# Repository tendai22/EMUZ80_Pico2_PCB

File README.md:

# EMUZ80_Pico2_PCB
KiCad PCB for emuz80_pico2

## WeAct RP2350B Core Board での動作

GPIO23を D7 に割り当てているが、D7 だけ L に落ちてくれない。

一瞬 L になるが、次の瞬間に H に戻っている。

blink で GPIO23 を指定したときは動作している。

Pimoroni 2350 の試作基板では動作している。

ハードウェアの違いによると考えられる。

基板の配線違いか、5.1kΩのプルアップが悪さをしていると考えた。

導通を見る限り怪しいところとつながっている様子はない。

結局 5.1kΩプルアップ抵抗をちぎり取って動作するようになった。なんとも。

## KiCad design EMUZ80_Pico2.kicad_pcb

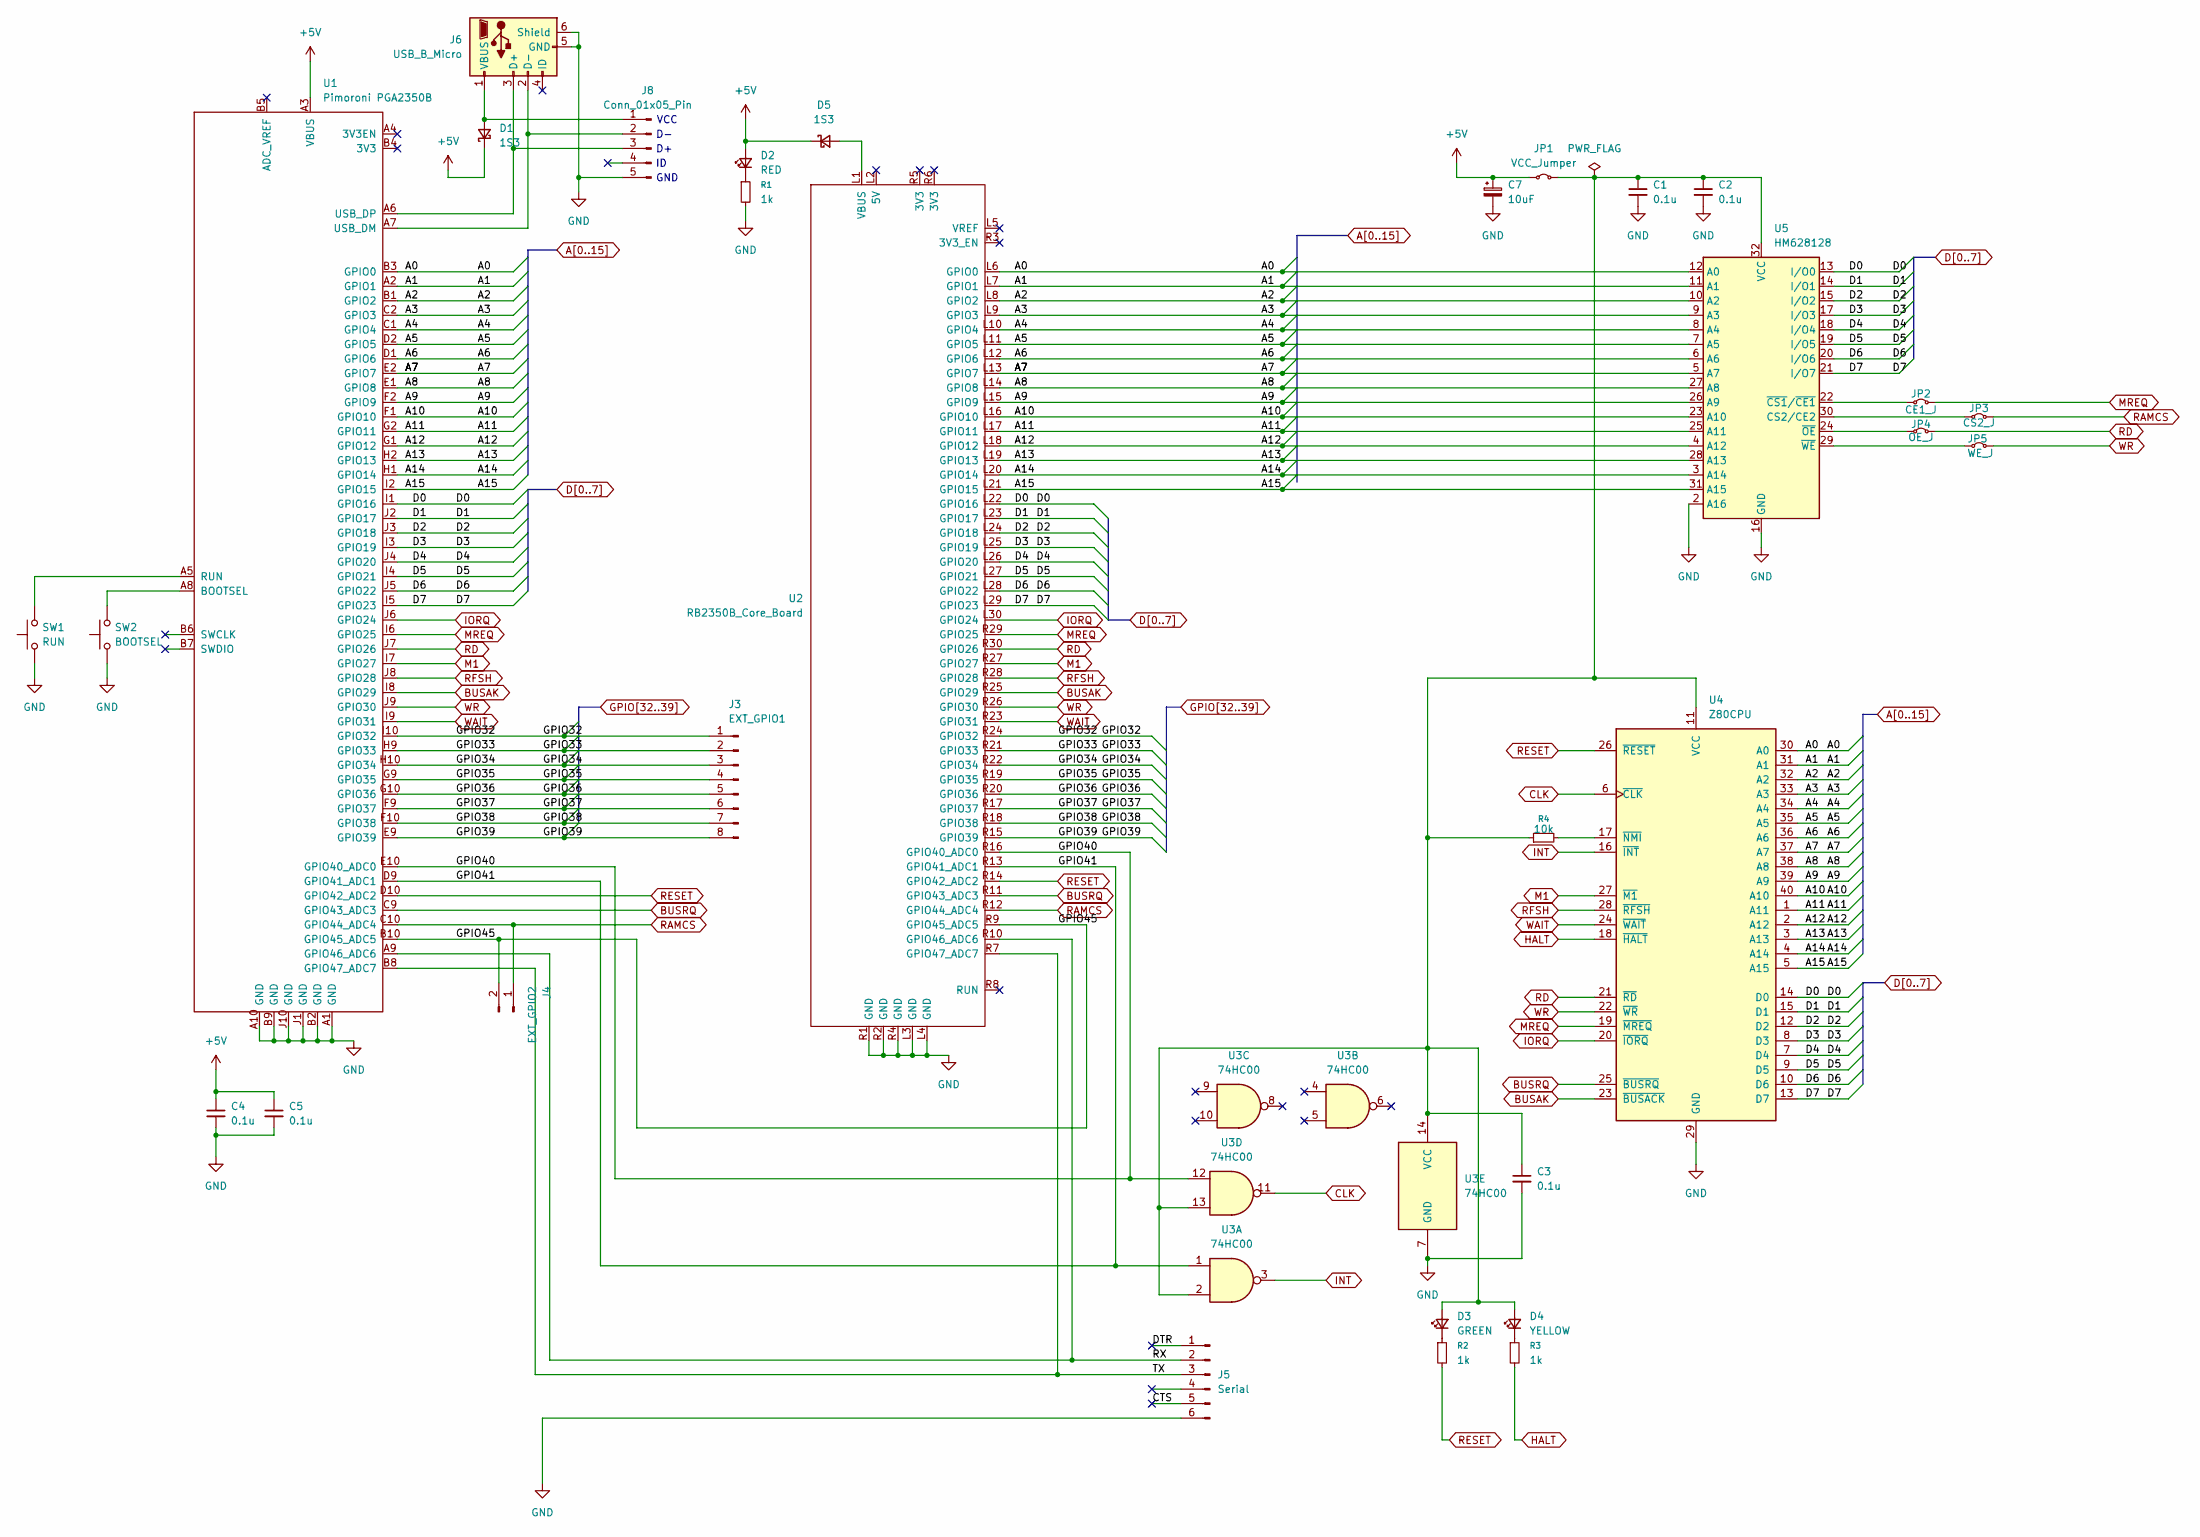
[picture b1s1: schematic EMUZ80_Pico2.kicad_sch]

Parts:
C1, C2, C3, C4, C5: 0.1u; C_Disc_D3.0mm_W1.6mm_P2.50mm
C7: 10uF; CP_Radial_D5.0mm_P2.50mm
D1, D5: 1S3; D_DO-34_SOD68_P7.62mm_Horizontal
D2: RED; LED_D3.0mm
D3: GREEN; LED_D3.0mm
D4: YELLOW; LED_D3.0mm
J3: EXT_GPIO1; PinHeader_1x08_P2.54mm_Vertical
J4: EXT_GPIO2; PinHeader_1x02_P2.54mm_Vertical
J5: Serial; PinHeader_1x06_P2.54mm_Horizontal_NoFeet
J6: USB_B_Micro; USB_Micro-B_Hirose_ZX62-B-5PA
J8: Conn_01x05_Pin; PinHeader_1x05_P2.54mm_Vertical
JP1: VCC_Jumper; SolderJumper-2_P1.3mm_Bridged_RoundedPad1.0x1.5mm
JP2: CE1_J; SolderJumper-2_P1.3mm_Bridged_RoundedPad1.0x1.5mm
JP3: CS2_J; SolderJumper-2_P1.3mm_Bridged_RoundedPad1.0x1.5mm
JP4: OE_J; SolderJumper-2_P1.3mm_Bridged_RoundedPad1.0x1.5mm
JP5: WE_J; SolderJumper-2_P1.3mm_Bridged_RoundedPad1.0x1.5mm
R1, R2, R3: 1k; R_Axial_L5.5mm_D2.0mm_P7.62mm_Horizontal
R4: 10k; R_Axial_L5.5mm_D2.0mm_P7.62mm_Horizontal
SW1: RUN; Tact_SW
SW2: BOOTSEL; Tact_SW
U1: Pimoroni PGA2350B; PLCC-64_THT-Socket
U2: RB2350B_Core_Board
U3: 74HC00; DIP-14_W7.62mm_Socket
U4: Z80CPU; DIP-40_SidePin_Z80
U5: HM628128; DIP-32_W15.24mm_OvalPads

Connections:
+5V: C4.1, C5.1, C7.1, D1.1 (K), D2.2 (A), D5.1 (K), JP1.1 (A), U1.A3 (VBUS)
/CTS: J5.5
/DTR: J5.1
/GPIO40: U1.E10 (GPIO40_ADC0), U2.R16 (GPIO40_ADC0), U3.12
/GPIO41: U1.D9 (GPIO41_ADC1), U2.R13 (GPIO41_ADC1), U3.1
/GPIO45: J4.2, U1.B10 (GPIO45_ADC5), U2.R9 (GPIO45_ADC5)
/RX: J5.2, U1.A9 (GPIO46_ADC6), U2.R10 (GPIO46_ADC6)
/TX: J5.3, U1.B8 (GPIO47_ADC7), U2.R7 (GPIO47_ADC7)
A0: U1.B3 (GPIO0), U2.L6 (GPIO0), U4.30 (A0), U5.12 (A0)
A1: U1.A2 (GPIO1), U2.L7 (GPIO1), U4.31 (A1), U5.11 (A1)
A2: U1.B1 (GPIO2), U2.L8 (GPIO2), U4.32 (A2), U5.10 (A2)
A3: U1.C2 (GPIO3), U2.L9 (GPIO3), U4.33 (A3), U5.9 (A3)
A4: U1.C1 (GPIO4), U2.L10 (GPIO4), U4.34 (A4), U5.8 (A4)
A5: U1.D2 (GPIO5), U2.L11 (GPIO5), U4.35 (A5), U5.7 (A5)
A6: U1.D1 (GPIO6), U2.L12 (GPIO6), U4.36 (A6), U5.6 (A6)
A7: U1.E2 (GPIO7), U2.L13 (GPIO7), U4.37 (A7), U5.5 (A7)
A8: U1.E1 (GPIO8), U2.L14 (GPIO8), U4.38 (A8), U5.27 (A8)
A9: U1.F2 (GPIO9), U2.L15 (GPIO9), U4.39 (A9), U5.26 (A9)
A10: U1.F1 (GPIO10), U2.L16 (GPIO10), U4.40 (A10), U5.23 (A10)
A11: U1.G2 (GPIO11), U2.L17 (GPIO11), U4.1 (A11), U5.25 (A11)
A12: U1.G1 (GPIO12), U2.L18 (GPIO12), U4.2 (A12), U5.4 (A12)
A13: U1.H2 (GPIO13), U2.L19 (GPIO13), U4.3 (A13), U5.28 (A13)
A14: U1.H1 (GPIO14), U2.L20 (GPIO14), U4.4 (A14), U5.3 (A14)
A15: U1.I2 (GPIO15), U2.L21 (GPIO15), U4.5 (A15), U5.31 (A15)
BUSAK: U1.I8 (GPIO29), U2.R25 (GPIO29), U4.23 (~BUSACK)
BUSRQ: U1.C9 (GPIO43_ADC3), U2.R11 (GPIO43_ADC3), U4.25 (~BUSRQ)
CLK: U3.11, U4.6 (~CLK)
D0: U1.I1 (GPIO16), U2.L22 (GPIO16), U4.14 (D0), U5.13 (I/O0)
D1: U1.J2 (GPIO17), U2.L23 (GPIO17), U4.15 (D1), U5.14 (I/O1)
D2: U1.J3 (GPIO18), U2.L24 (GPIO18), U4.12 (D2), U5.15 (I/O2)
D3: U1.I3 (GPIO19), U2.L25 (GPIO19), U4.8 (D3), U5.17 (I/O3)
D4: U1.J4 (GPIO20), U2.L26 (GPIO20), U4.7 (D4), U5.18 (I/O4)
D5: U1.I4 (GPIO21), U2.L27 (GPIO21), U4.9 (D5), U5.19 (I/O5)
D6: U1.J5 (GPIO22), U2.L28 (GPIO22), U4.10 (D6), U5.20 (I/O6)
D7: U1.I5 (GPIO23), U2.L29 (GPIO23), U4.13 (D7), U5.21 (I/O7)
GND: C1.2, C2.2, C3.2, C4.2, C5.2, C7.2, J5.6, J6.5 (GND), J6.6 (Shield), J8.5, R1.2, SW1.1, SW2.1, U1.A1 (GND), U1.A10 (GND), U1.B2 (GND), U1.B9 (GND), U1.J1 (GND), U1.J10 (GND), U2.L3 (GND), U2.L4 (GND), U2.R1 (GND), U2.R2 (GND), U2.R4 (GND), U3.7 (GND), U4.29 (GND), U5.2 (A16), U5.16 (GND)
GPIO32: J3.1, U1.I10 (GPIO32), U2.R24 (GPIO32)
GPIO33: J3.2, U1.H9 (GPIO33), U2.R21 (GPIO33)
GPIO34: J3.3, U1.H10 (GPIO34), U2.R22 (GPIO34)
GPIO35: J3.4, U1.G9 (GPIO35), U2.R19 (GPIO35)
GPIO36: J3.5, U1.G10 (GPIO36), U2.R20 (GPIO36)
GPIO37: J3.6, U1.F9 (GPIO37), U2.R17 (GPIO37)
GPIO38: J3.7, U1.F10 (GPIO38), U2.R18 (GPIO38)
GPIO39: J3.8, U1.E9 (GPIO39), U2.R15 (GPIO39)
HALT: R3.2, U4.18 (~HALT)
INT: U3.3, U4.16 (~INT)
IORQ: U1.J6 (GPIO24), U2.L30 (GPIO24), U4.20 (~IORQ)
M1: U1.I7 (GPIO27), U2.R27 (GPIO27), U4.27 (~M1)
MREQ: JP2.2 (B), U1.I6 (GPIO25), U2.R29 (GPIO25), U4.19 (~MREQ)
unnamed: D1.2 (A), J6.1 (VBUS), J8.1
unnamed: D2.1 (K), R1.1
unnamed: C1.1, C2.1, C3.1, D3.2 (A), D4.2 (A), JP1.2 (B), R4.1, U3.2, U3.13, U3.14 (VCC), U4.11 (VCC), U5.32 (VCC)
unnamed: D3.1 (K), R2.1
unnamed: D4.1 (K), R3.1
unnamed: D5.2 (A), U2.L1 (VBUS)
unnamed: J6.3 (D+), J8.3, U1.A6 (USB_DP)
unnamed: J6.2 (D-), J8.2, U1.A7 (USB_DM)
unnamed: JP2.1 (A), U5.22 (~CS1/~CE1)
unnamed: JP3.1 (A), U5.30 (CS2/CE2)
unnamed: JP4.1 (A), U5.24 (~OE)
unnamed: JP5.1 (A), U5.29 (~WE)
unnamed: SW2.2, U1.A8 (BOOTSEL)
unnamed: SW1.2, U1.A5 (RUN)
unnamed: R4.2, U4.17 (~NMI)
RAMCS: J4.1, JP3.2 (B), U1.C10 (GPIO44_ADC4), U2.R12 (GPIO44_ADC4)
RD: JP4.2 (B), U1.J7 (GPIO26), U2.R30 (GPIO26), U4.21 (~RD)
RESET: R2.2, U1.D10 (GPIO42_ADC2), U2.R14 (GPIO42_ADC2), U4.26 (~RESET)
RFSH: U1.J8 (GPIO28), U2.R28 (GPIO28), U4.28 (~RFSH)
WAIT: U1.I9 (GPIO31), U2.R23 (GPIO31), U4.24 (~WAIT)
WR: JP5.2 (B), U1.J9 (GPIO30), U2.R26 (GPIO30), U4.22 (~WR)

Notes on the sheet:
GND
VCC

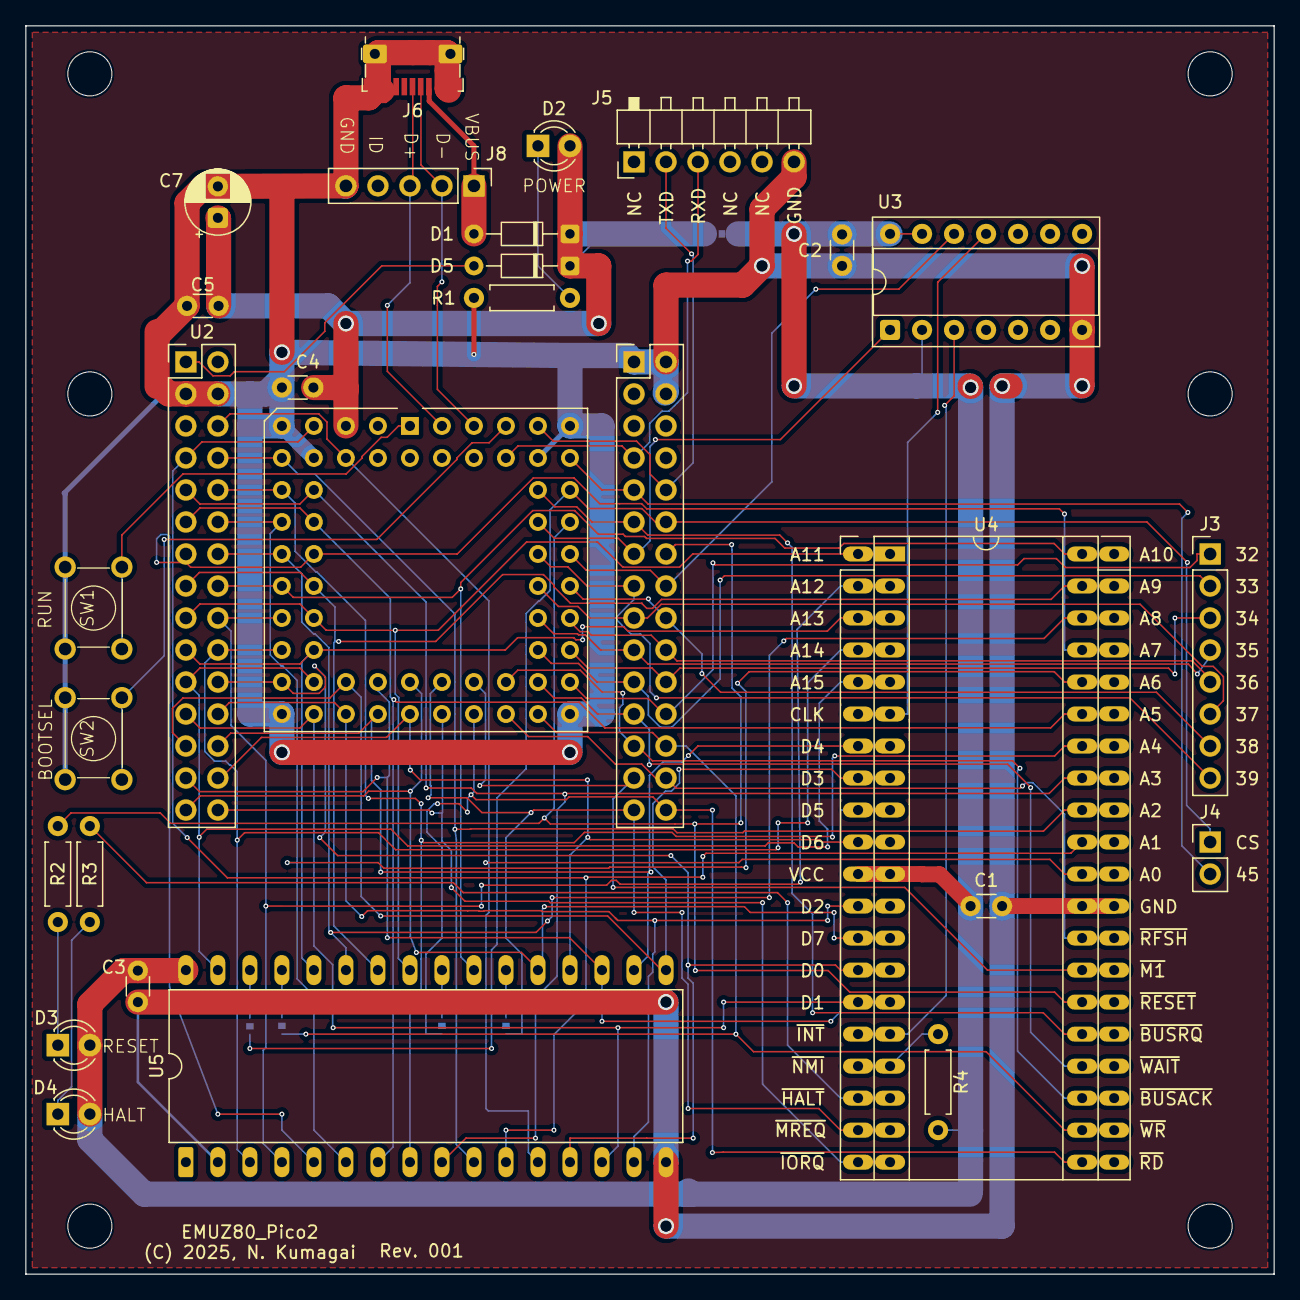
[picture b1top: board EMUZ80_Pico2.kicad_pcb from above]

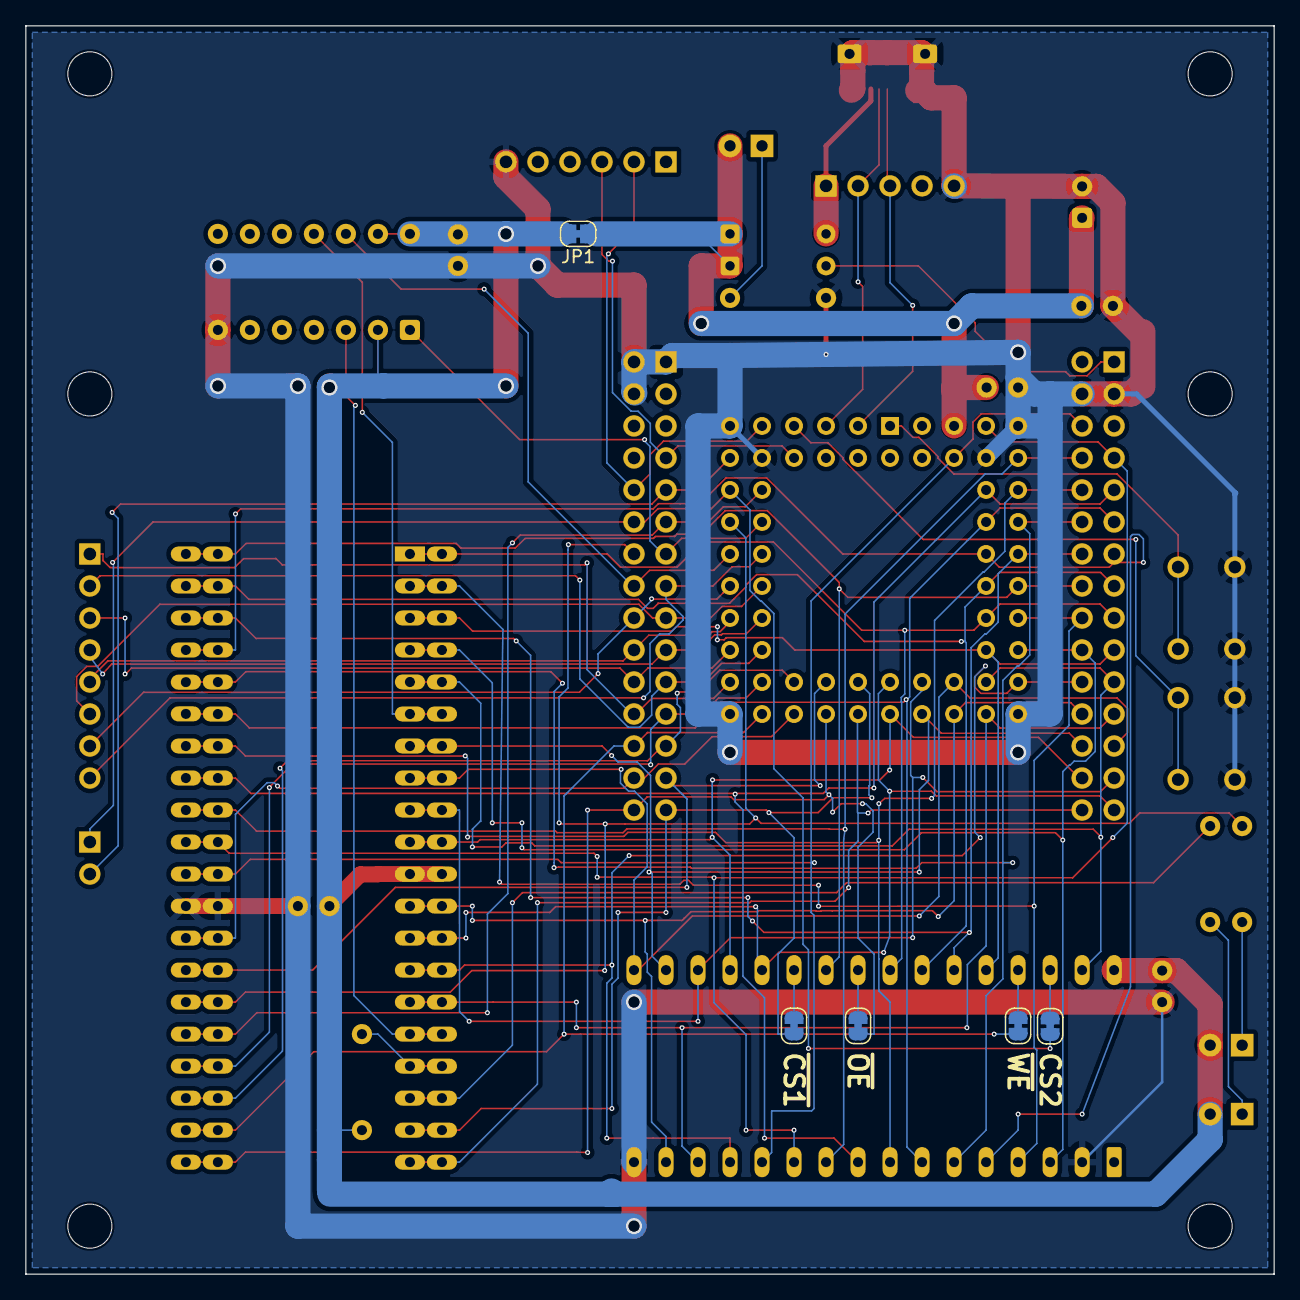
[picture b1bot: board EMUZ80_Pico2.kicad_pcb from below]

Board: 2 copper layers, 99.1 x 99.1 mm, 38 parts (5 on the bottom side), 68 nets.

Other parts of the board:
H1, H2, H3, H4, H5, H6: MountingHole; MountingHole_3.5mm

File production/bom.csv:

Designator,Footprint,Quantity,Value,LCSC Part #
"C1, C2, C3, C4, C5",C_Disc_D3.0mm_W1.6mm_P2.50mm,5,0.1u,
C7,CP_Radial_D5.0mm_P2.50mm,1,10uF,
"D1, D5",D_DO-34_SOD68_P7.62mm_Horizontal,2,1S3,
D2,LED_D3.0mm,1,RED,
D3,LED_D3.0mm,1,GREEN,
D4,LED_D3.0mm,1,YELLOW,
J3,PinHeader_1x08_P2.54mm_Vertical,1,EXT_GPIO1,
J4,PinHeader_1x02_P2.54mm_Vertical,1,EXT_GPIO2,
J5,PinHeader_1x06_P2.54mm_Horizontal_NoFeet,1,Serial,
J6,USB_Micro-B_Hirose_ZX62-B-5PA,1,USB_B_Micro,
J8,PinHeader_1x05_P2.54mm_Vertical,1,Conn_01x05_Pin,
JP1,SolderJumper-2_P1.3mm_Bridged_RoundedPad1.0x1.5mm,1,VCC_Jumper,
JP2,SolderJumper-2_P1.3mm_Bridged_RoundedPad1.0x1.5mm,1,CE1_J,
JP3,SolderJumper-2_P1.3mm_Bridged_RoundedPad1.0x1.5mm,1,CS2_J,
JP4,SolderJumper-2_P1.3mm_Bridged_RoundedPad1.0x1.5mm,1,OE_J,
JP5,SolderJumper-2_P1.3mm_Bridged_RoundedPad1.0x1.5mm,1,WE_J,
"R1, R2, R3",R_Axial_L5.5mm_D2.0mm_P7.62mm_Horizontal,3,1k,
R4,R_Axial_L5.5mm_D2.0mm_P7.62mm_Horizontal,1,10k,
SW1,Tact_SW,1,RUN,
SW2,Tact_SW,1,BOOTSEL,
U1,PLCC-64_THT-Socket,1,Pimoroni PGA2350B,
U2,RB2350B_Core_Board,1,RB2350B_Core_Board,
U3,DIP-14_W7.62mm_Socket,1,74HC00,
U4,DIP-40_SidePin_Z80,1,Z80CPU,
U5,DIP-32_W15.24mm_OvalPads,1,HM628128,

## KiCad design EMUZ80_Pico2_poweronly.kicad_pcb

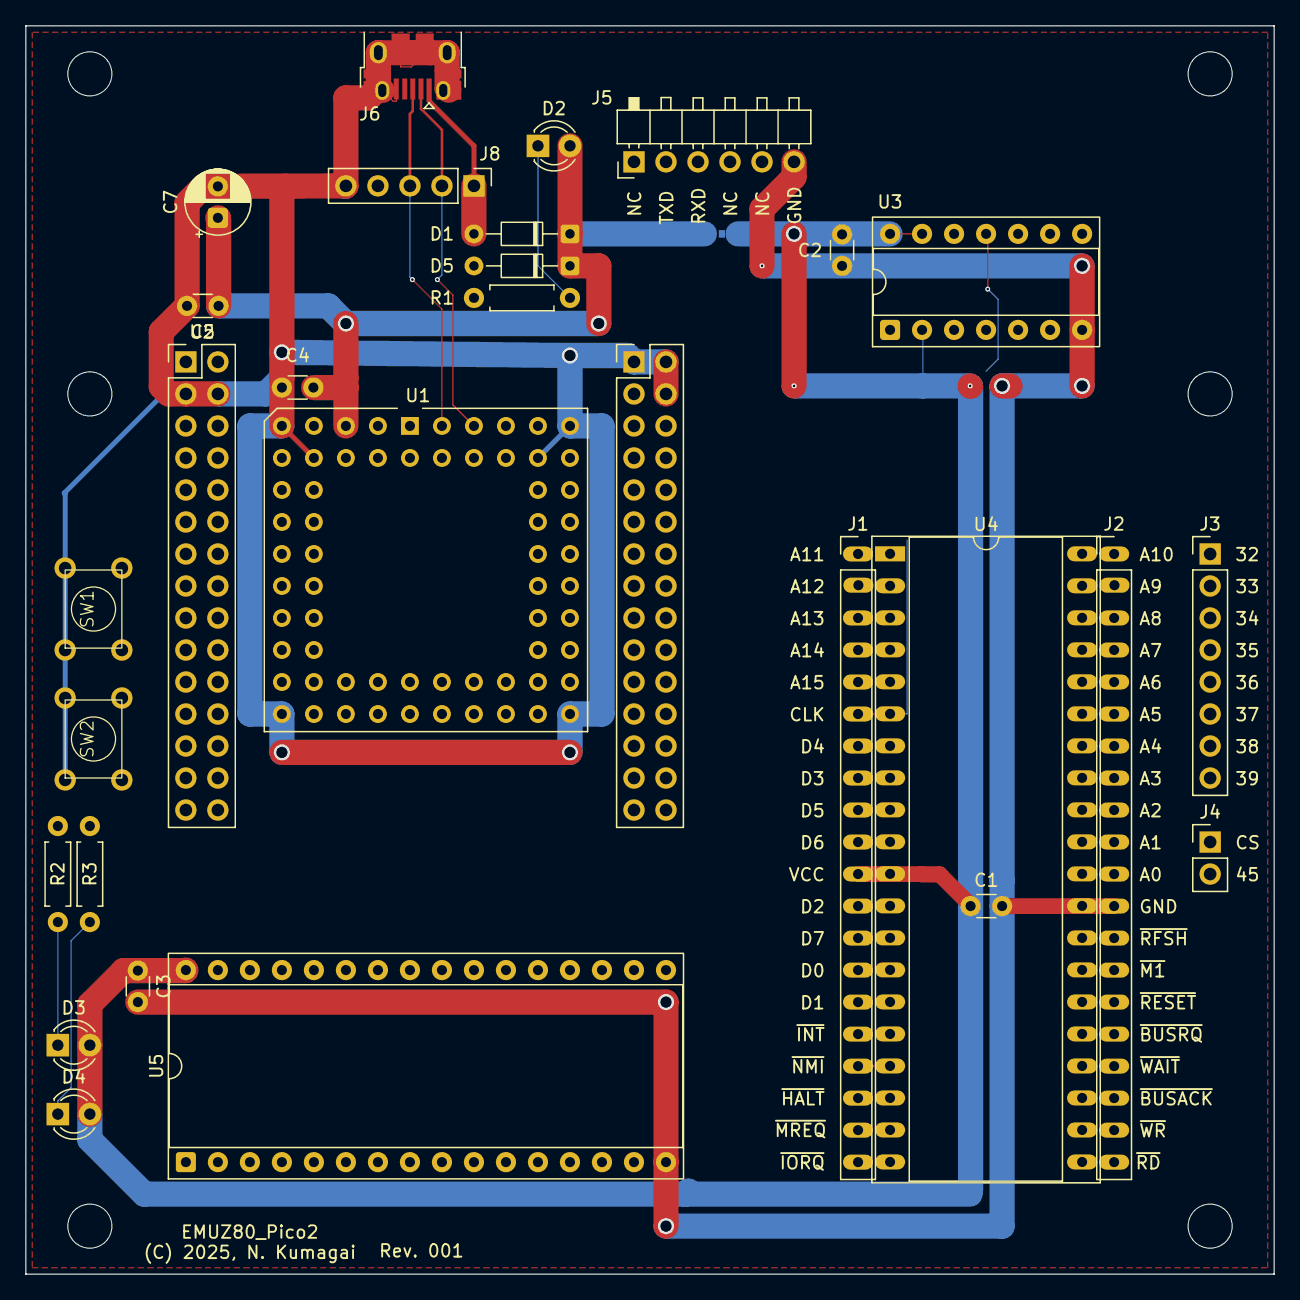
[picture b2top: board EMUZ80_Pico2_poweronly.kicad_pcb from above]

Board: 2 copper layers, 99.1 x 99.1 mm, 35 parts (1 on the bottom side), 64 nets.

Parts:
C1, C2, C3, C4, C5: 0.1u; C_Disc_D3.0mm_W1.6mm_P2.50mm
C7: 10uF; CP_Radial_D5.0mm_P2.50mm
D1, D5: 1S3; D_DO-34_SOD68_P7.62mm_Horizontal
D2: RED; LED_D3.0mm
D3: GREEN; LED_D3.0mm
D4: YELLOW; LED_D3.0mm
H1, H2, H3, H4, H5, H6: MountingHole; MountingHole_3.5mm
J1: Z80_L; PinHeader_1x20_P2.54mm_Ovalpad_Vertical
J2: Z80_R; PinHeader_1x20_P2.54mm_Ovalpad_Vertical
J3: EXT_GPIO1; PinHeader_1x08_P2.54mm_Vertical
J4: EXT_GPIO2; PinHeader_1x02_P2.54mm_Vertical
J5: Serial; PinHeader_1x06_P2.54mm_Horizontal_NoFeet
J6: USB_B_Micro; USB_Micro-B_Amphenol_10103594-0001LF_Horizontal
J8: Conn_01x05_Pin; PinHeader_1x05_P2.54mm_Vertical
JP1: VCC_Jumper; SolderJumper-2_P1.3mm_Bridged_RoundedPad1.0x1.5mm
R1, R2, R3: 1k; R_Axial_L5.5mm_D2.0mm_P7.62mm_Horizontal
SW1: RUN; Tact_SW
SW2: BOOTSEL; Tact_SW
U1: Pimoroni PGA2350B; PLCC-64_THT-Socket
U2: RB2350B_Core_Board
U3: 74HC00; DIP-14_W7.62mm_Socket
U4: Z80CPU; DIP-40_W15.24mm_Socket_OvalPad_splitcouryard
U5: HM628128; DIP-32_W15.24mm_Socket

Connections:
+5V: C4.1, C5.1, C7.1, D1.1 (K), D2.2 (A), D5.1 (K), JP1.1 (A), U1.A3 (VBUS)
/GPIO40: U1.E10 (GPIO40_ADC0), U2.R16 (GPIO40_ADC0), U3.12
/GPIO41: U1.D9 (GPIO41_ADC1), U2.R13 (GPIO41_ADC1), U3.1
/GPIO45: J4.2, U1.B10 (GPIO45_ADC5), U2.R9 (GPIO45_ADC5)
/RX: J5.2, U1.A9 (GPIO46_ADC6), U2.R10 (GPIO46_ADC6)
/TX: J5.3, U1.B8 (GPIO47_ADC7), U2.R7 (GPIO47_ADC7)
/VCC: C1.1, C2.1, C3.1, D3.2 (A), D4.2 (A), J1.11, JP1.2 (B), U3.2, U3.13, U3.14 (VCC), U4.11 (VCC), U5.32 (VCC)
A0: J2.11, U1.B3 (GPIO0), U2.L6 (GPIO0), U4.30 (A0), U5.12 (A0)
A1: J2.10, U1.A2 (GPIO1), U2.L7 (GPIO1), U4.31 (A1), U5.11 (A1)
A2: J2.9, U1.B1 (GPIO2), U2.L8 (GPIO2), U4.32 (A2), U5.10 (A2)
A3: J2.8, U1.C2 (GPIO3), U2.L9 (GPIO3), U4.33 (A3), U5.9 (A3)
A4: J2.7, U1.C1 (GPIO4), U2.L10 (GPIO4), U4.34 (A4), U5.8 (A4)
A5: J2.6, U1.D2 (GPIO5), U2.L11 (GPIO5), U4.35 (A5), U5.7 (A5)
A6: J2.5, U1.D1 (GPIO6), U2.L12 (GPIO6), U4.36 (A6), U5.6 (A6)
A7: J2.4, U1.E2 (GPIO7), U2.L13 (GPIO7), U4.37 (A7), U5.5 (A7)
A8: J2.3, U1.E1 (GPIO8), U2.L14 (GPIO8), U4.38 (A8), U5.27 (A8)
A9: J2.2, U1.F2 (GPIO9), U2.L15 (GPIO9), U4.39 (A9), U5.26 (A9)
A10: J2.1, U1.F1 (GPIO10), U2.L16 (GPIO10), U4.40 (A10), U5.23 (A10)
A11: J1.1, U1.G2 (GPIO11), U2.L17 (GPIO11), U4.1 (A11), U5.25 (A11)
A12: J1.2, U1.G1 (GPIO12), U2.L18 (GPIO12), U4.2 (A12), U5.4 (A12)
A13: J1.3, U1.H2 (GPIO13), U2.L19 (GPIO13), U4.3 (A13), U5.28 (A13)
A14: J1.4, U1.H1 (GPIO14), U2.L20 (GPIO14), U4.4 (A14), U5.3 (A14)
A15: J1.5, U1.I2 (GPIO15), U2.L21 (GPIO15), U4.5 (A15), U5.31 (A15)
BUSAK: J2.18, U1.I8 (GPIO29), U2.R25 (GPIO29), U4.23 (~BUSACK)
BUSRQ: J2.16, U1.C9 (GPIO43_ADC3), U2.R11 (GPIO43_ADC3), U4.25 (~BUSRQ)
CLK: J1.6, U3.11, U4.6 (~CLK)
D0: J1.14, U1.I1 (GPIO16), U2.L22 (GPIO16), U4.14 (D0), U5.13 (I/O0)
D1: J1.15, U1.J2 (GPIO17), U2.L23 (GPIO17), U4.15 (D1), U5.14 (I/O1)
D2: J1.12, U1.J3 (GPIO18), U2.L24 (GPIO18), U4.12 (D2), U5.15 (I/O2)
D3: J1.8, U1.I3 (GPIO19), U2.L25 (GPIO19), U4.8 (D3), U5.17 (I/O3)
D4: J1.7, U1.J4 (GPIO20), U2.L26 (GPIO20), U4.7 (D4), U5.18 (I/O4)
D5: J1.9, U1.I4 (GPIO21), U2.L27 (GPIO21), U4.9 (D5), U5.19 (I/O5)
D6: J1.10, U1.J5 (GPIO22), U2.L28 (GPIO22), U4.10 (D6), U5.20 (I/O6)
D7: J1.13, U1.I5 (GPIO23), U2.L29 (GPIO23), U4.13 (D7), U5.21 (I/O7)
GND: C1.2, C2.2, C3.2, C4.2, C5.2, C7.2, J2.12, J5.6, J6.5 (GND), J6.6 (Shield), J8.5, R1.2, SW1.1, SW2.1, U1.A1 (GND), U1.A10 (GND), U1.B2 (GND), U1.B9 (GND), U1.J1 (GND), U1.J10 (GND), U2.L3 (GND), U2.L4 (GND), U2.R1 (GND), U2.R2 (GND), U2.R4 (GND), U3.7 (GND), U4.29 (GND), U5.2 (A16), U5.16 (GND)
GPIO32: J3.1, U1.I10 (GPIO32), U2.R24 (GPIO32)
GPIO33: J3.2, U1.H9 (GPIO33), U2.R21 (GPIO33)
GPIO34: J3.3, U1.H10 (GPIO34), U2.R22 (GPIO34)
GPIO35: J3.4, U1.G9 (GPIO35), U2.R19 (GPIO35)
GPIO36: J3.5, U1.G10 (GPIO36), U2.R20 (GPIO36)
GPIO37: J3.6, U1.F9 (GPIO37), U2.R17 (GPIO37)
GPIO38: J3.7, U1.F10 (GPIO38), U2.R18 (GPIO38)
GPIO39: J3.8, U1.E9 (GPIO39), U2.R15 (GPIO39)
HALT: J1.18, R3.2, U4.18 (~HALT)
INT: J1.16, U3.3, U4.16 (~INT)
IORQ: J1.20, U1.J6 (GPIO24), U2.L30 (GPIO24), U4.20 (~IORQ)
M1: J2.14, U1.I7 (GPIO27), U2.R27 (GPIO27), U4.27 (~M1)
MREQ: J1.19, U1.I6 (GPIO25), U2.R29 (GPIO25), U4.19 (~MREQ), U5.22 (~CS1/~CE1)
NMI: J1.17, U4.17 (~NMI)
unnamed: D1.2 (A), J6.1 (VBUS), J8.1
unnamed: D2.1 (K), R1.1
unnamed: D3.1 (K), R2.1
unnamed: D4.1 (K), R3.1
unnamed: D5.2 (A), U2.L1 (VBUS)
unnamed: J6.3 (D+), J8.3, U1.A6 (USB_DP)
unnamed: J6.2 (D-), J8.2, U1.A7 (USB_DM)
unnamed: SW2.2, U1.A8 (BOOTSEL)
unnamed: SW1.2, U1.A5 (RUN)
RAMCS: J4.1, U1.C10 (GPIO44_ADC4), U2.R12 (GPIO44_ADC4), U5.30 (CS2/CE2)
RD: J2.20, U1.J7 (GPIO26), U2.R30 (GPIO26), U4.21 (~RD), U5.24 (~OE)
RESET: J2.15, R2.2, U1.D10 (GPIO42_ADC2), U2.R14 (GPIO42_ADC2), U4.26 (~RESET)
RFSH: J2.13, U1.J8 (GPIO28), U2.R28 (GPIO28), U4.28 (~RFSH)
WAIT: J2.17, U1.I9 (GPIO31), U2.R23 (GPIO31), U4.24 (~WAIT)
WR: J2.19, U1.J9 (GPIO30), U2.R26 (GPIO30), U4.22 (~WR), U5.29 (~WE)

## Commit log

2025-06-03 add essential files
2025-06-03 schematic finished
2025-06-04 imported two DIP-40 footprints and one 1x20 PinHeader footprint
2025-06-04 schematic done, pcb now working
2025-06-05 EMUZ80_Pico2: PCB routing completed, ready to order
2025-06-06 PCB rev001 finished, ready to order JLCPCB
2025-06-07 add JP2-5 to SRAM Controls
2025-06-07 Rev001: order data
2025-11-16 RP2350B Core Board does not work will, remove 5.1k R on the RP2305B Core Board, bad behavior

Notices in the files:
EMUZ80_Pico2.kicad_pcb:
(C) 2025, N. Kumagai
